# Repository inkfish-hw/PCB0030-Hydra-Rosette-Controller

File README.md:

# PCB0030-Hydra-Rosette-Controller

These are replacement electronics for Hydra's Niskin rosette for more control over sampling

**Designer:** Brian Ramos

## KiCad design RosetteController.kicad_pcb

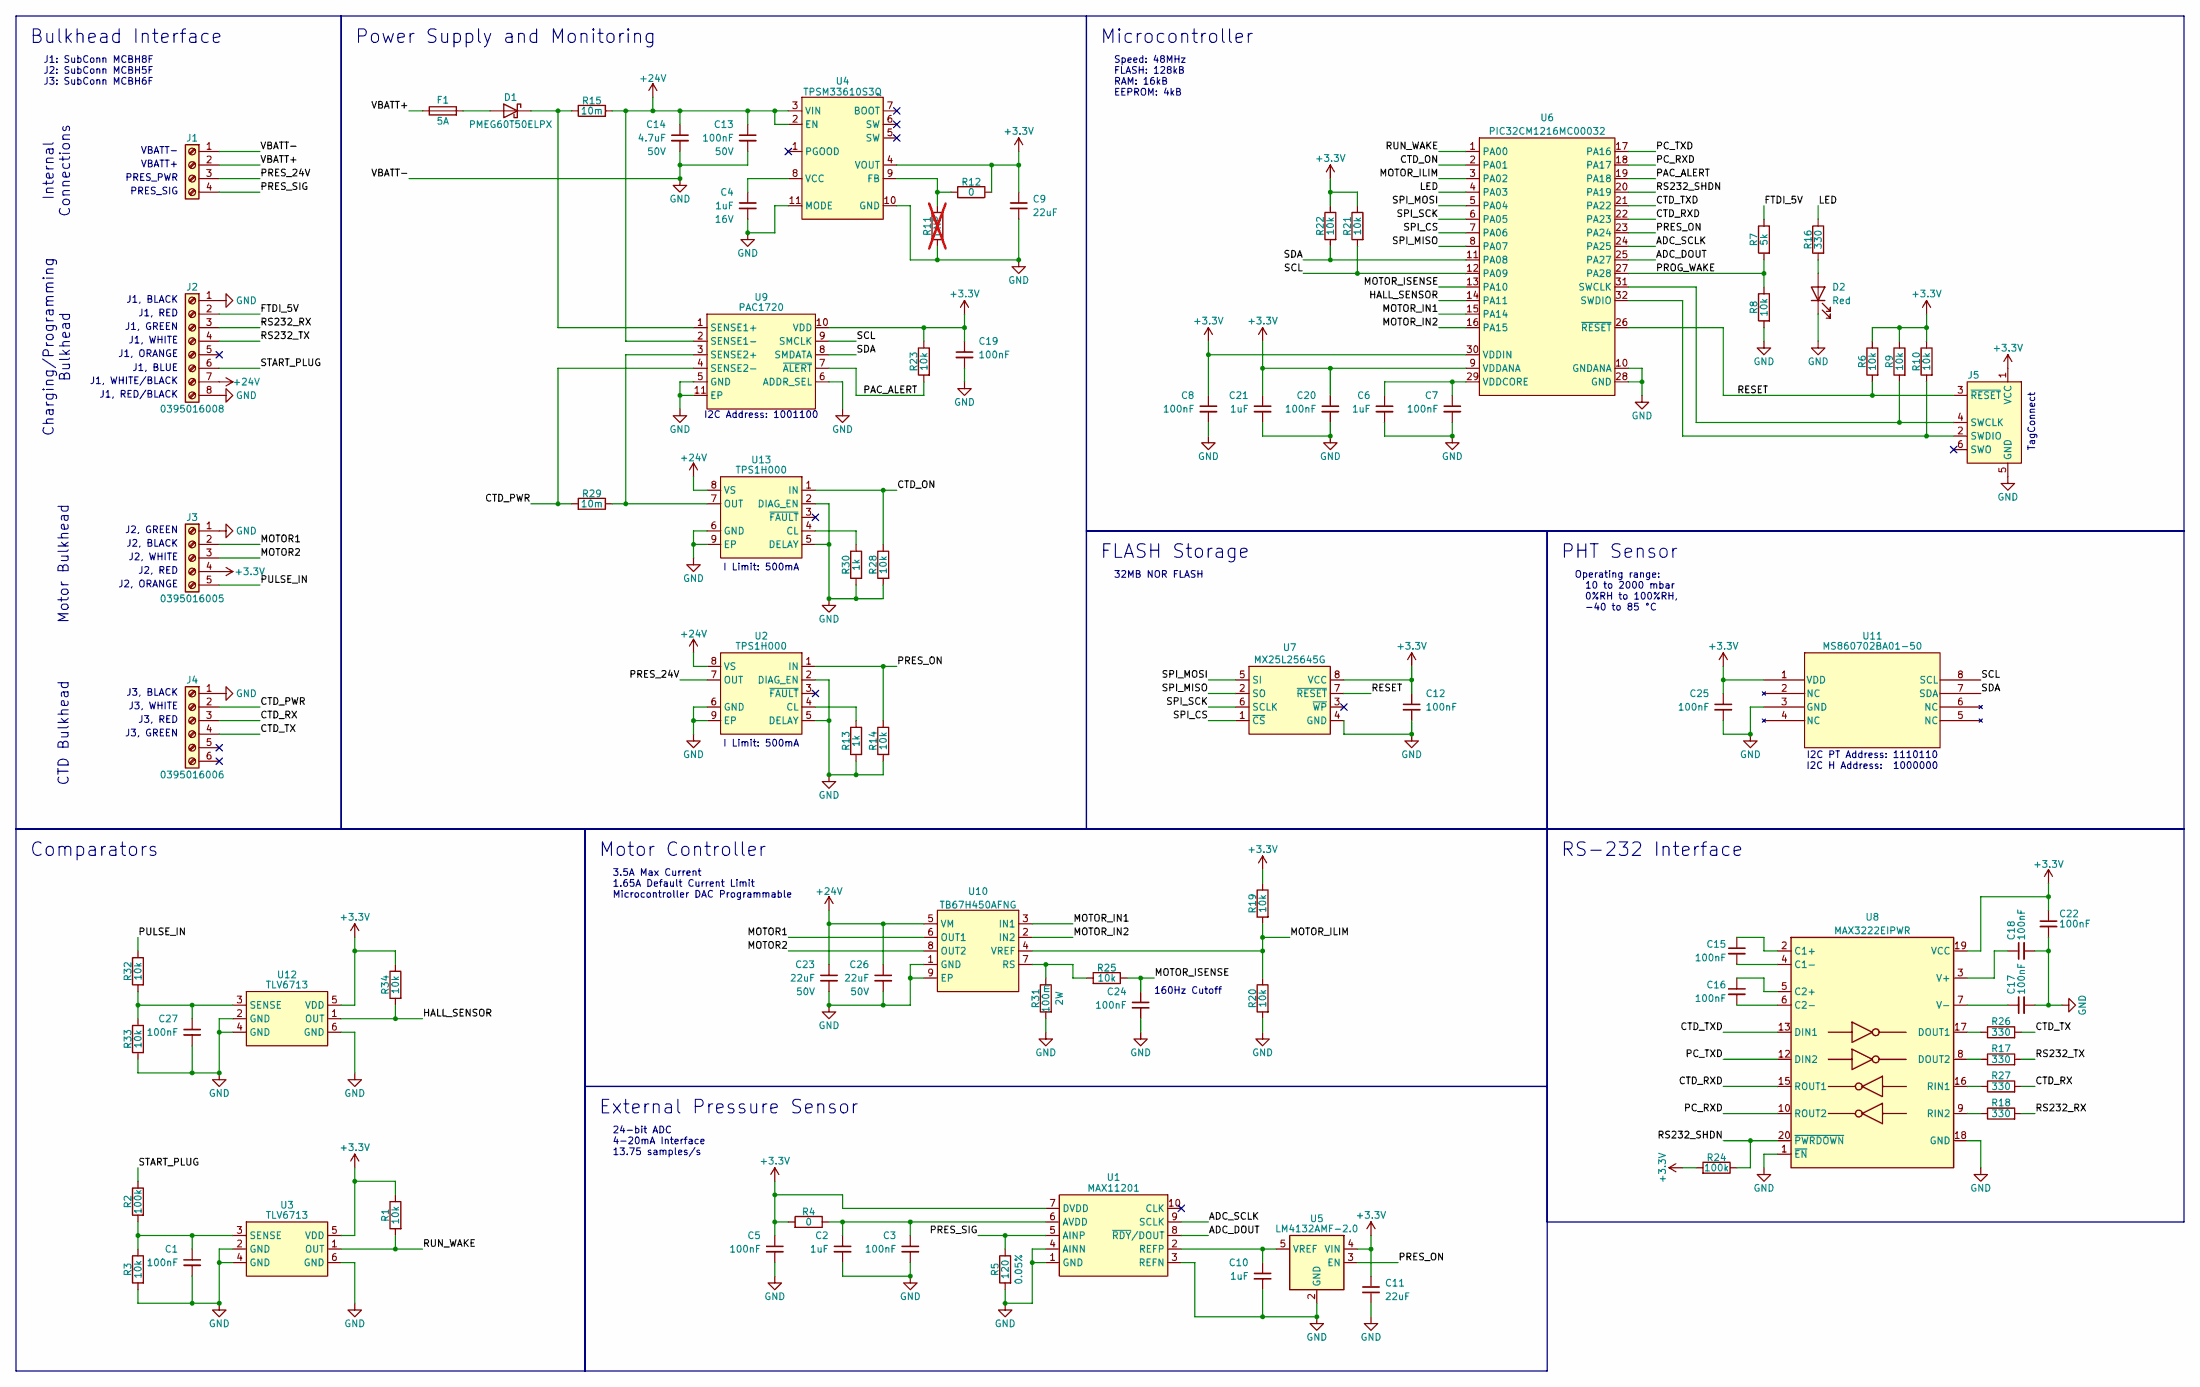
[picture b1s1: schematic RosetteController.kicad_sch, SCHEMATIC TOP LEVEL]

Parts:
C1, C3, C5, C7, C8, C12, C13, C19, C20, C24, C25, C27: 100nF; C_0402_1005Metric; VoltageRating 50V; MPN GCM155R71H104KE02D
C2, C4, C6, C10, C21: 1uF; C_0402_1005Metric; VoltageRating 16V; MPN GRM155C81C105ME11J
C9, C11: 22uF; C_0603_1608Metric; MPN GRT188R61A226ME13D
C14: 4.7uF; C_0805_2012Metric; VoltageRating 50V; MPN GRM21BR61H475KE51L
C15, C16, C17, C18, C22: 100nF; C_0402_1005Metric; MPN GCM155R71H104KE02D
C23, C26: 22uF; C_2220_5750Metric; VoltageRating 50V; MPN C5750X7R1H226M250KB
D1: PMEG60T50ELPX; D_SOD-128; MPN PMEG60T50ELPX
D2: LTST-C191KRKT; LED_0603_1608Metric; Manufacturer Part Number LTST-C191KRKT
F1: 5A; Fuse_1206_3216Metric; MPN 0685T5000-01
J1: 0395016004; PhoenixContact_MCV_1,5_4-G-3.5_1x04_P3.50mm_Vertical; MPN 0395016004
J2: 0395016008; PhoenixContact_MCV_1,5_8-G-3.5_1x08_P3.50mm_Vertical; MPN 0395016008
J3: 0395016005; PhoenixContact_MCV_1,5_5-G-3.5_1x05_P3.50mm_Vertical; MPN 0395016005
J4: 0395016006; PhoenixContact_MCV_1,5_6-G-3.5_1x06_P3.50mm_Vertical; MPN 0395016006
J5: Conn_ARM_SWD_TagConnect_TC2030; Tag-Connect_TC2030-IDC-NL_2x03_P1.27mm_Vertical
R1, R3, R6, R8, R9, R10, R14, R19, R20, R21, R22, R23, R25, R28, R32, R33, R34: 10k; R_0402_1005Metric; MPN ERJ-2RKF1002X
R2, R24: 100k; R_0402_1005Metric; MPN ERJ-2RKF1003X
R4, R12: 0; R_0402_1005Metric; MPN ERJ-2GE0R00X
R5: 120; R_0805_2012Metric; Tolerance 0.05%; MPN RG2012N-121-W-T1
R7: 5k; R_0402_1005Metric; MPN RC0402FR-075KL
R11: DNP; R_0402_1005Metric; not fitted
R13, R30: 1k; R_0402_1005Metric; MPN RC0402FR-071KL
R15, R29: 10m; R_0805_2012Metric; MPN WSLP0805R0100FEA
R16, R17, R18, R26, R27: 330; R_0402_1005Metric; MPN RC0402FR-07330RL
R31: 100m; R_2010_5025Metric; MPN CSNL2010FTR100
U1: MAX11201; MSOP-10_3x3mm_P0.5mm; MPN MAX11201BEUB+
U2, U13: TPS1H000; HVSSOP-8-1EP_3x3mm_P0.65mm_EP1.57x1.89mm_ThermalVias; MPN TPS1H000AQDGNRQ1
U3, U12: TLV6713; TSOT-23-6; MPN TLV6713DDCR
U4: TPSM33610S3Q; U_QFN-FCMOD_RDN0011B_TEX; MPN TPSM33610S3QRDNRQ1
U5: LM4132AMF-2.0; SOT-23-5; MPN LM4132AMF-2.0/NOPB
U6: PIC32CM1216MC00032; TQFP-32_7x7mm_P0.8mm; MPN PIC32CM1216MC00032T-E/PT
U7: MX25L25645G; SOIC-8_5.3x5.3mm_P1.27mm; MPN MX25L25645GM2I-08G
U8: MAX3222EIPWR; Texas_PW0020A_TSSOP-20_4.4x6.5mm_P0.65mm; MPN MAX3222EIPWR
U9: PAC1720; DFN-10-1EP_3x3mm_P0.5mm_EP1.65x2.38mm_ThermalVias; MPN PAC1720-1-AIA-TR
U10: TB67H450AFNG; SOIC-8-1EP_3.9x4.9mm_P1.27mm_EP2.29x3mm; MPN TB67H450AFNG,EL
U11: MS860702BA01-50; MS860702BA01-50_TEC; Manufacturer Part Number MS860702BA01-50

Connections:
+3.3V: C5.1, C8.1, C9.1, C11.1, C12.1, C19.1, C20.1, C21.1, C22.1, C25.1, J3.4, J5.1 (VCC), R1.1, R4.2, R6.1, R9.1, R10.1, R12.1, R19.1, R21.1, R22.1, R23.1, R24.2, R34.1, U1.7 (DVDD), U3.5 (VDD), U4.4 (VOUT), U5.4 (VIN), U6.9 (VDDANA), U6.30 (VDDIN), U7.8 (VCC), U8.19 (VCC), U9.10 (VDD), U11.1 (VDD), U12.5 (VDD)
+24V: C13.1, C14.1, C23.1, C26.1, J2.7, R15.2, U2.8 (VS), U4.2 (EN), U4.3 (VIN), U9.2 (SENSE1-), U10.5 (VM), U13.8 (VS)
/ADC_DOUT: U1.8 (~RDY/DOUT), U6.25 (PA27)
/ADC_SCLK: U1.9 (SCLK), U6.24 (PA25)
/CTD_ON: R28.1, U6.2 (PA01), U13.1 (IN)
/CTD_PWR: J4.2, R29.2, U9.4 (SENSE2-)
/CTD_RX: J4.3, R27.2
/CTD_RXD: U6.22 (PA23), U8.15 (ROUT1)
/CTD_TX: J4.4, R26.2
/CTD_TXD: U6.21 (PA22), U8.13 (DIN1)
/FTDI_5V: J2.2, R7.1
/HALL_SENSOR: R34.2, U6.14 (PA11), U12.1 (OUT)
/LED: R16.1, U6.4 (PA03)
/MOTOR1: J3.2, U10.6 (OUT1)
/MOTOR2: J3.3, U10.8 (OUT2)
/MOTOR_ILIM: R19.2, R20.1, U6.3 (PA02), U10.4 (VREF)
/MOTOR_IN1: U6.15 (PA14), U10.3 (IN1)
/MOTOR_IN2: U6.16 (PA15), U10.2 (IN2)
/MOTOR_ISENSE: C24.1, R25.1, U6.13 (PA10)
/PAC_ALERT: R23.2, U6.19 (PA18), U9.7 (~ALERT)
/PC_RXD: U6.18 (PA17), U8.10 (ROUT2)
/PC_TXD: U6.17 (PA16), U8.12 (DIN2)
/PRES_24V: J1.3, U2.7 (OUT)
/PRES_ON: R14.1, U2.1 (IN), U5.3 (EN), U6.23 (PA24)
/PRES_SIG: J1.4, R5.1, U1.5 (AINP)
/PROG_WAKE: R7.2, R8.1, U6.27 (PA28)
/PULSE_IN: J3.5, R32.1
/RESET: J5.3 (~RESET), R6.2, U6.26 (~RESET), U7.7 (~RESET)
/RS232_RX: J2.3, R18.2
/RS232_SHDN: R24.1, U6.20 (PA19), U8.20 (~PWRDOWN)
/RS232_TX: J2.4, R17.2
/RUN_WAKE: R1.2, U3.1 (OUT), U6.1 (PA00)
/SCL: R21.2, U6.12 (PA09), U9.9 (SMCLK), U11.8 (SCL)
/SDA: R22.2, U6.11 (PA08), U9.8 (SMDATA), U11.7 (SDA)
/SPI_CS: U6.7 (PA06), U7.1 (~CS)
/SPI_MISO: U6.8 (PA07), U7.2 (SO)
/SPI_MOSI: U6.5 (PA04), U7.5 (SI)
/SPI_SCK: U6.6 (PA05), U7.6 (SCLK)
/START_PLUG: J2.6, R2.1
/VBATT+: F1.1, J1.2
GND: C1.2, C2.2, C3.2, C4.2, C5.2, C6.2, C7.2, C8.2, C9.2, C10.2, C11.2, C12.2, C13.2, C14.2, C17.2, C18.2, C19.2, C20.2, C21.2, C22.2, C23.2, C24.2, C25.2, C26.2, C27.2, D2.1 (K), J1.1, J2.1, J2.8, J3.1, J4.1, J5.5 (GND), R3.2, R5.2, R8.2, R11.2, R13.2, R14.2, R20.2, R28.2, R30.2, R31.2, R33.2, U1.1 (GND), U1.3 (REFN), U1.4 (AINN), U2.2 (DIAG_EN), U2.5 (DELAY), U2.6 (GND), U2.9 (EP), U3.2 (GND), U3.4 (GND), U3.6 (GND), U4.10 (GND), U4.11 (MODE), U5.2 (GND), U6.10 (GNDANA), U6.28 (GND), U7.4 (GND), U8.1 (~EN), U8.18 (GND), U9.5 (GND), U9.6 (ADDR_SEL), U9.11 (EP), U10.1 (GND), U10.9 (EP), U11.3 (GND), U12.2 (GND), U12.4 (GND), U12.6 (GND), U13.2 (DIAG_EN), U13.5 (DELAY), U13.6 (GND), U13.9 (EP)
unnamed: D2.2 (A), R16.2
unnamed: D1.2 (A), F1.2
unnamed: D1.1 (K), R15.1, U9.1 (SENSE1+)
unnamed: J5.4 (SWCLK), R9.2, U6.31 (SWCLK)
unnamed: J5.2 (SWDIO), R10.2, U6.32 (SWDIO)
unnamed: C6.1, C7.1, U6.29 (VDDCORE)
unnamed: C15.1, U8.2 (C1+)
unnamed: C15.2, U8.4 (C1-)
unnamed: C16.1, U8.5 (C2+)
unnamed: C16.2, U8.6 (C2-)
unnamed: R26.1, U8.17 (DOUT1)
unnamed: R17.1, U8.8 (DOUT2)
unnamed: R27.1, U8.16 (RIN1)
unnamed: R18.1, U8.9 (RIN2)
unnamed: C18.1, U8.3 (V+)
unnamed: C17.1, U8.7 (V-)
unnamed: R11.1, R12.2, U4.9 (FB)
unnamed: C4.1, U4.8 (VCC)
unnamed: C10.1, U1.2 (REFP), U5.5 (VREF)
unnamed: C2.1, C3.1, R4.1, U1.6 (AVDD)
unnamed: R25.2, R31.1, U10.7 (RS)
unnamed: C1.1, R2.2, R3.1, U3.3 (SENSE)
unnamed: R29.1, U9.3 (SENSE2+), U13.7 (OUT)
unnamed: R30.1, U13.4 (CL)
unnamed: R13.1, U2.4 (CL)
unnamed: C27.1, R32.2, R33.1, U12.3 (SENSE)

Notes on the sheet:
VBATT+
I2C Address: 1001100
3.5A Max Current 1.65A Default Current Limit Microcontroller DAC Programmable
PHT Sensor
J1, RED/BLACK
VBATT-
J1, GREEN
Comparators
Charging/Programming Bulkhead
RS-232 Interface
J2, WHITE
J2, RED
Bulkhead Interface
J3, WHITE
CTD Bulkhead
J2, ORANGE
I Limit: 500mA
PRES_SIG
J1, WHITE/BLACK
24-bit ADC 4-20mA Interface 13.75 samples/s
32MB NOR FLASH
Motor Bulkhead
I2C PT Address: 1110110 I2C H Address: 1000000
J3, GREEN
J1, WHITE
J1: SubConn MCBH8F J2: SubConn MCBH5F J3: SubConn MCBH6F
Microcontroller
160Hz Cutoff
J2, GREEN
Speed: 48MHz FLASH: 128kB RAM: 16kB EEPROM: 4kB
TagConnect
J2, BLACK
Motor Controller
J1, BLACK
FLASH Storage
PRES_PWR
J1, BLUE
J3, RED
J3, BLACK
Internal Connections

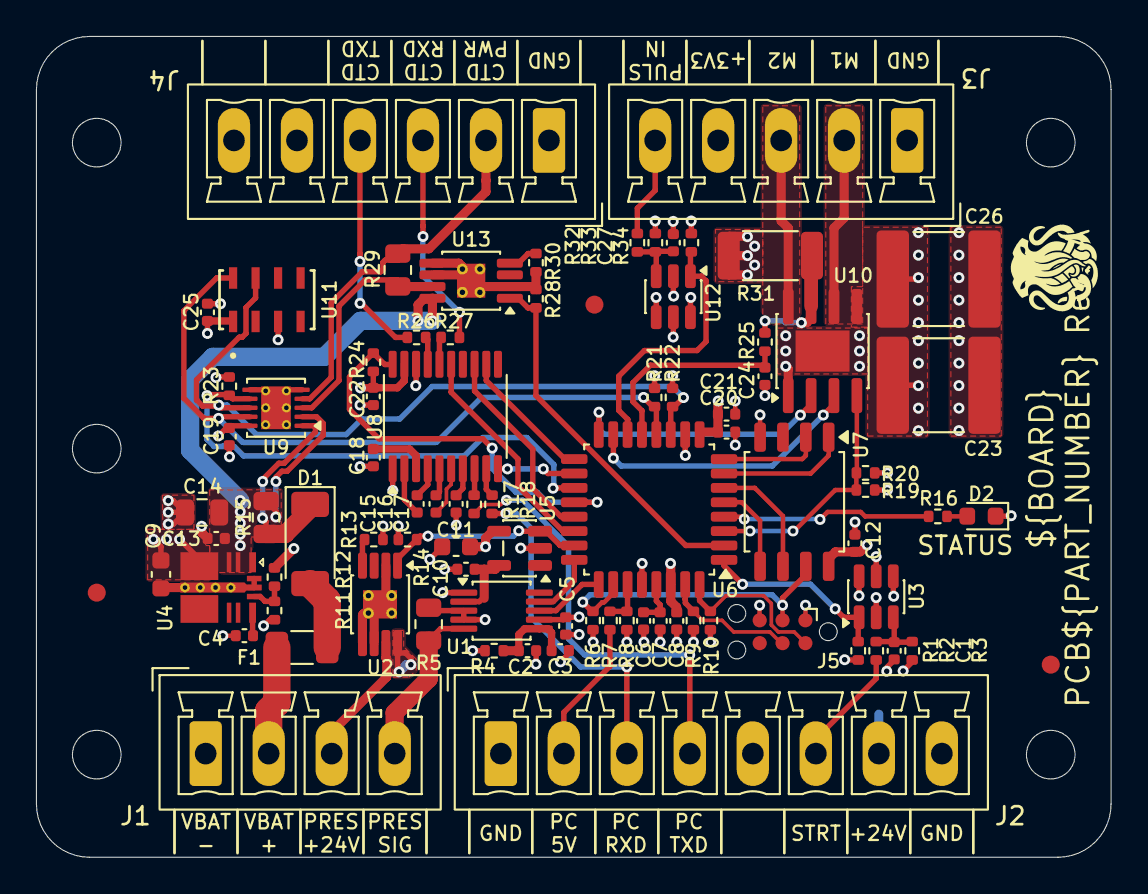
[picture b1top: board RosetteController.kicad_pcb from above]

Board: 4 copper layers, 59.7 x 45.6 mm, 91 parts (0 on the bottom side), 67 nets.

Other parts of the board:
FID1, FID2, FID3: Fiducial_1mm_Mask3mm
G1: LOGO
M1, M2, M3, M4, M5: MountingHole_2.7mm_M2.5
